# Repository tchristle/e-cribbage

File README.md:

# e-cribbage
SMT LED Cribbage Board

**To-Do List**
**-----------------------------------------------------------------**
* Schematic
	- [x] assign different symbols to P1 and P2 LEDs
	- [x] assign correct parts numbers to switch and CR2032 symbols
	- [ ] assign final values to LED current limiting resistor
* Layout
	- [x] modify CR2032 footprint to match selected clip
	- [x] modify B5 footprint to match selected slide switch
	- [x] assign common footprint to all capacitors
	- [x] update footprint for S1-S4 tactile push buttons
	- [x] generate gerbers and drill
	- [ ] fix up silk screen on foot prints
* Mechanical
	- [ ] design acrylic cover
	- [ ] update view showing current buttons
* BOM
	- [x] generate BOM from KiCAD schematic
	- [ ] attach Digikey PNs to BOM
	- [X] down select LEDs and colors
	- [x] down select slide switch
	- [x] down select tactile push button
	- [ ] generate Digikey cart from BOM
	- [x] get pricing on PCB
	- [x] get pricing on stencils
	- [ ] get pricing on pick and place assembly
* Software
	- [ ] debug flash store and recall functions
	- [ ] replace for loops and counters with timers in LPM0
	- [X] implement peg swap timer
	- [X] implement Elapsed Time Indicator
* Prototype
	- [x] drive sample LEDs with limit resistor to set brightness level
	- [X] analyze battery life with CR2032 cell
	- [x] interface ez430 with single shifter register

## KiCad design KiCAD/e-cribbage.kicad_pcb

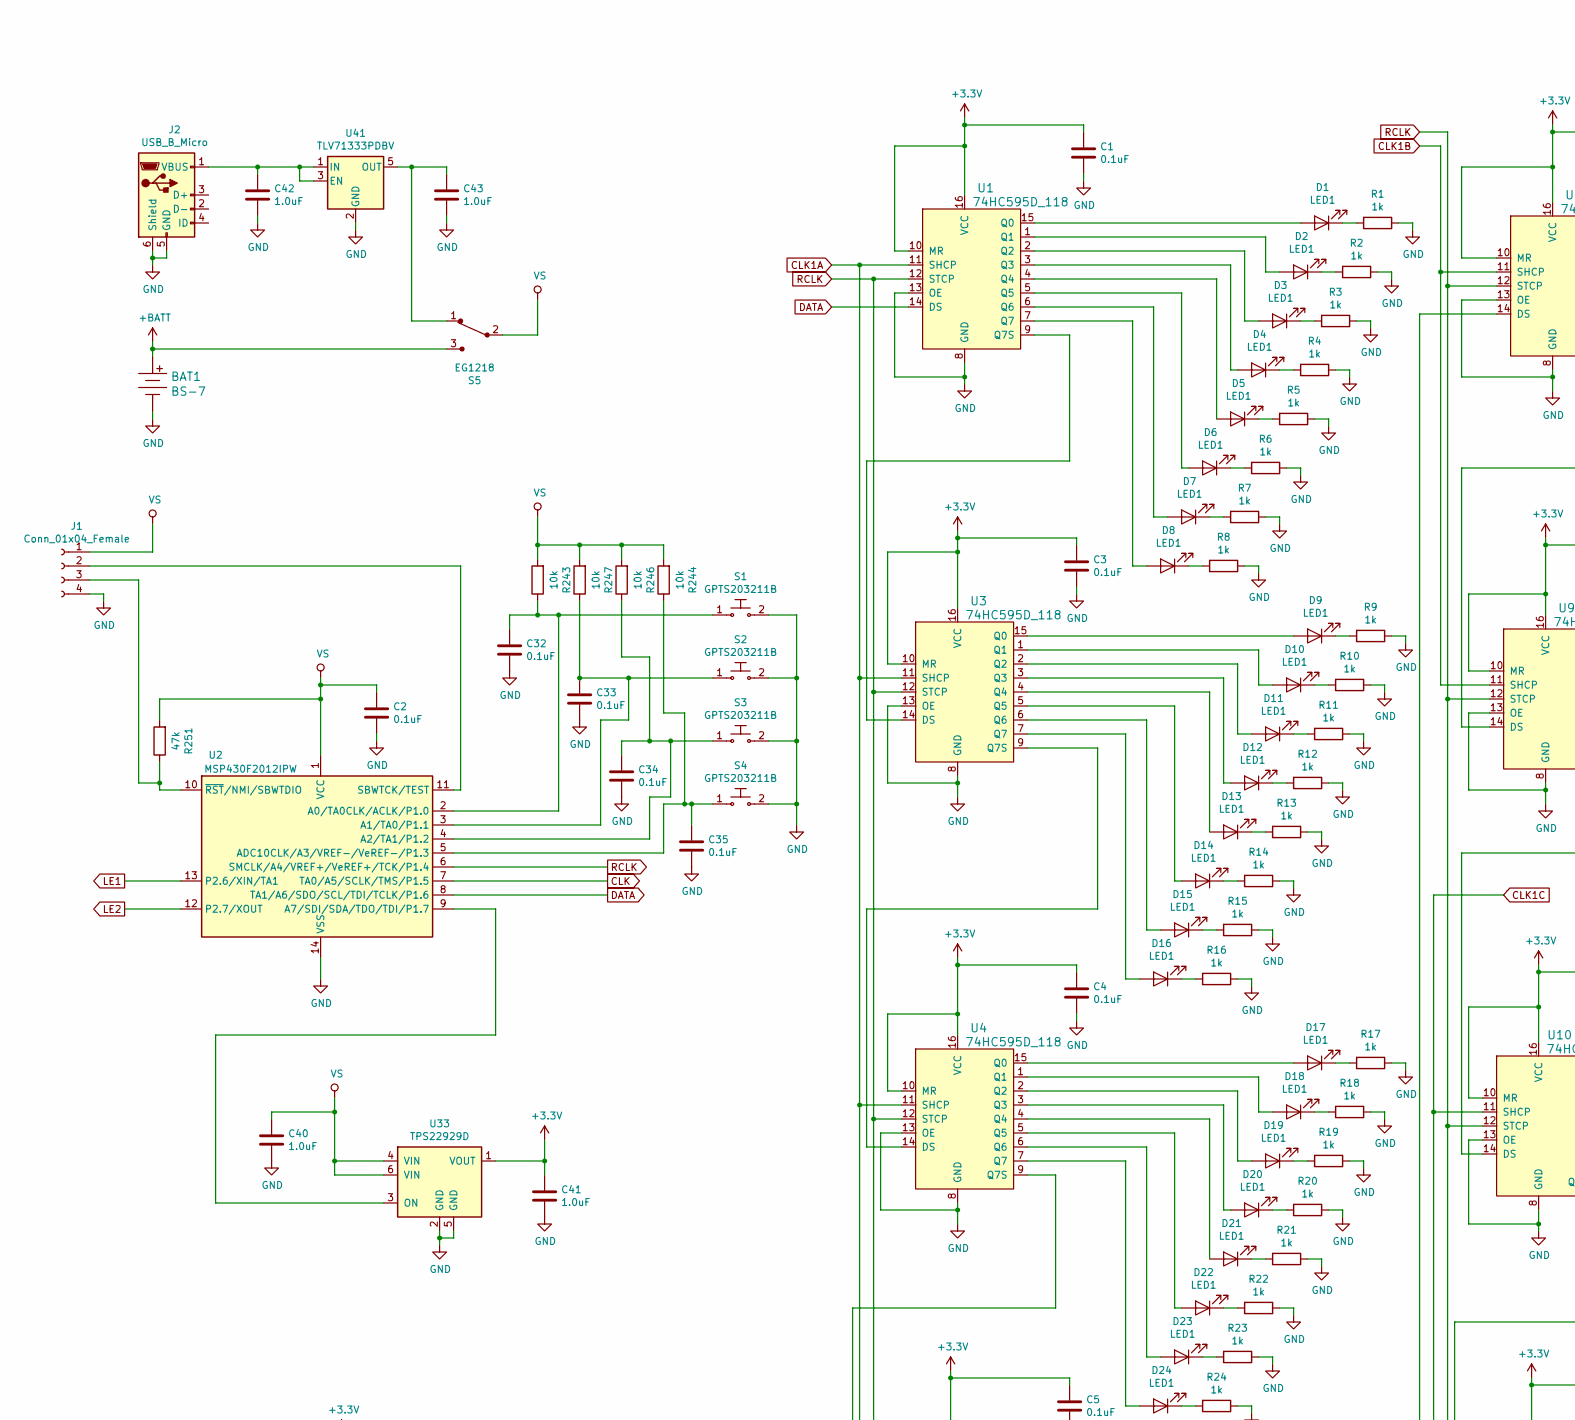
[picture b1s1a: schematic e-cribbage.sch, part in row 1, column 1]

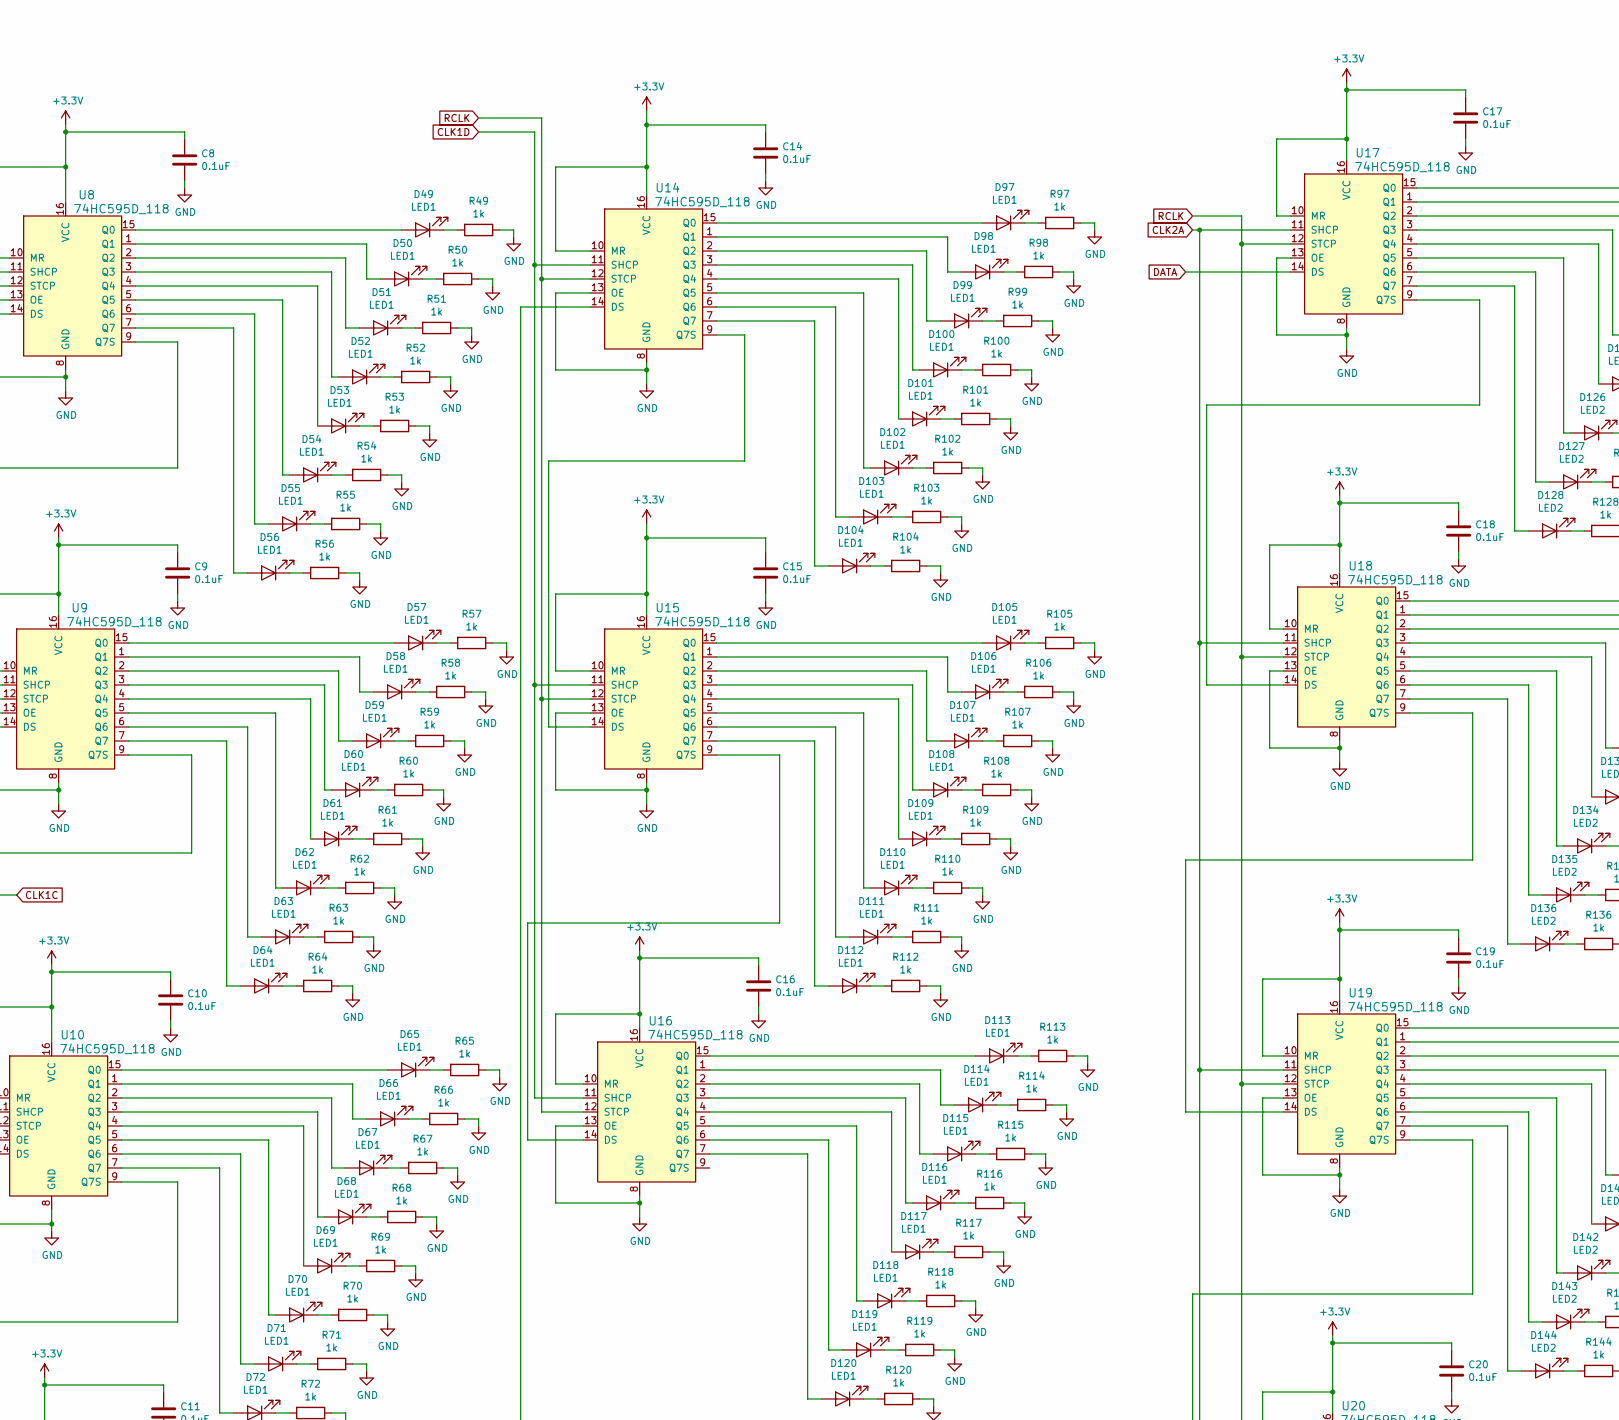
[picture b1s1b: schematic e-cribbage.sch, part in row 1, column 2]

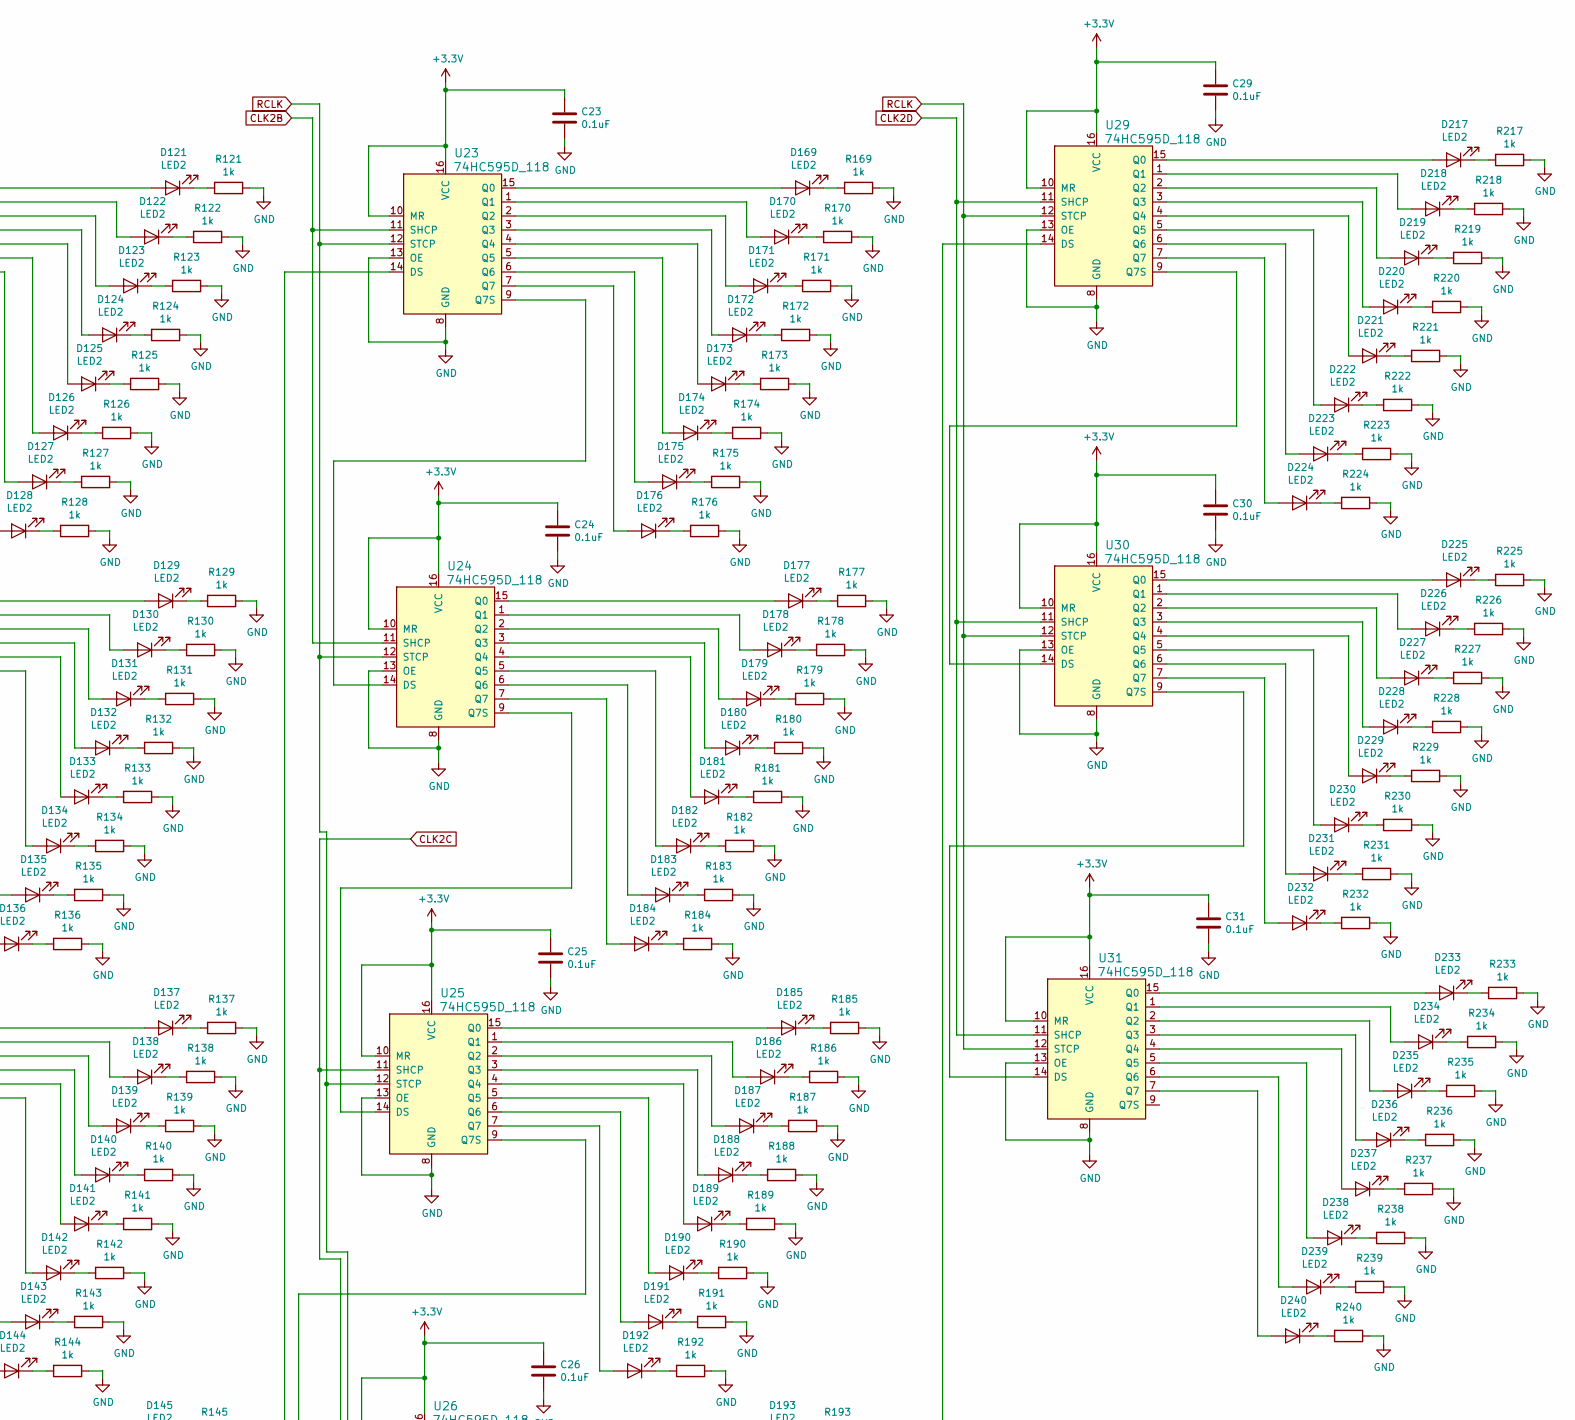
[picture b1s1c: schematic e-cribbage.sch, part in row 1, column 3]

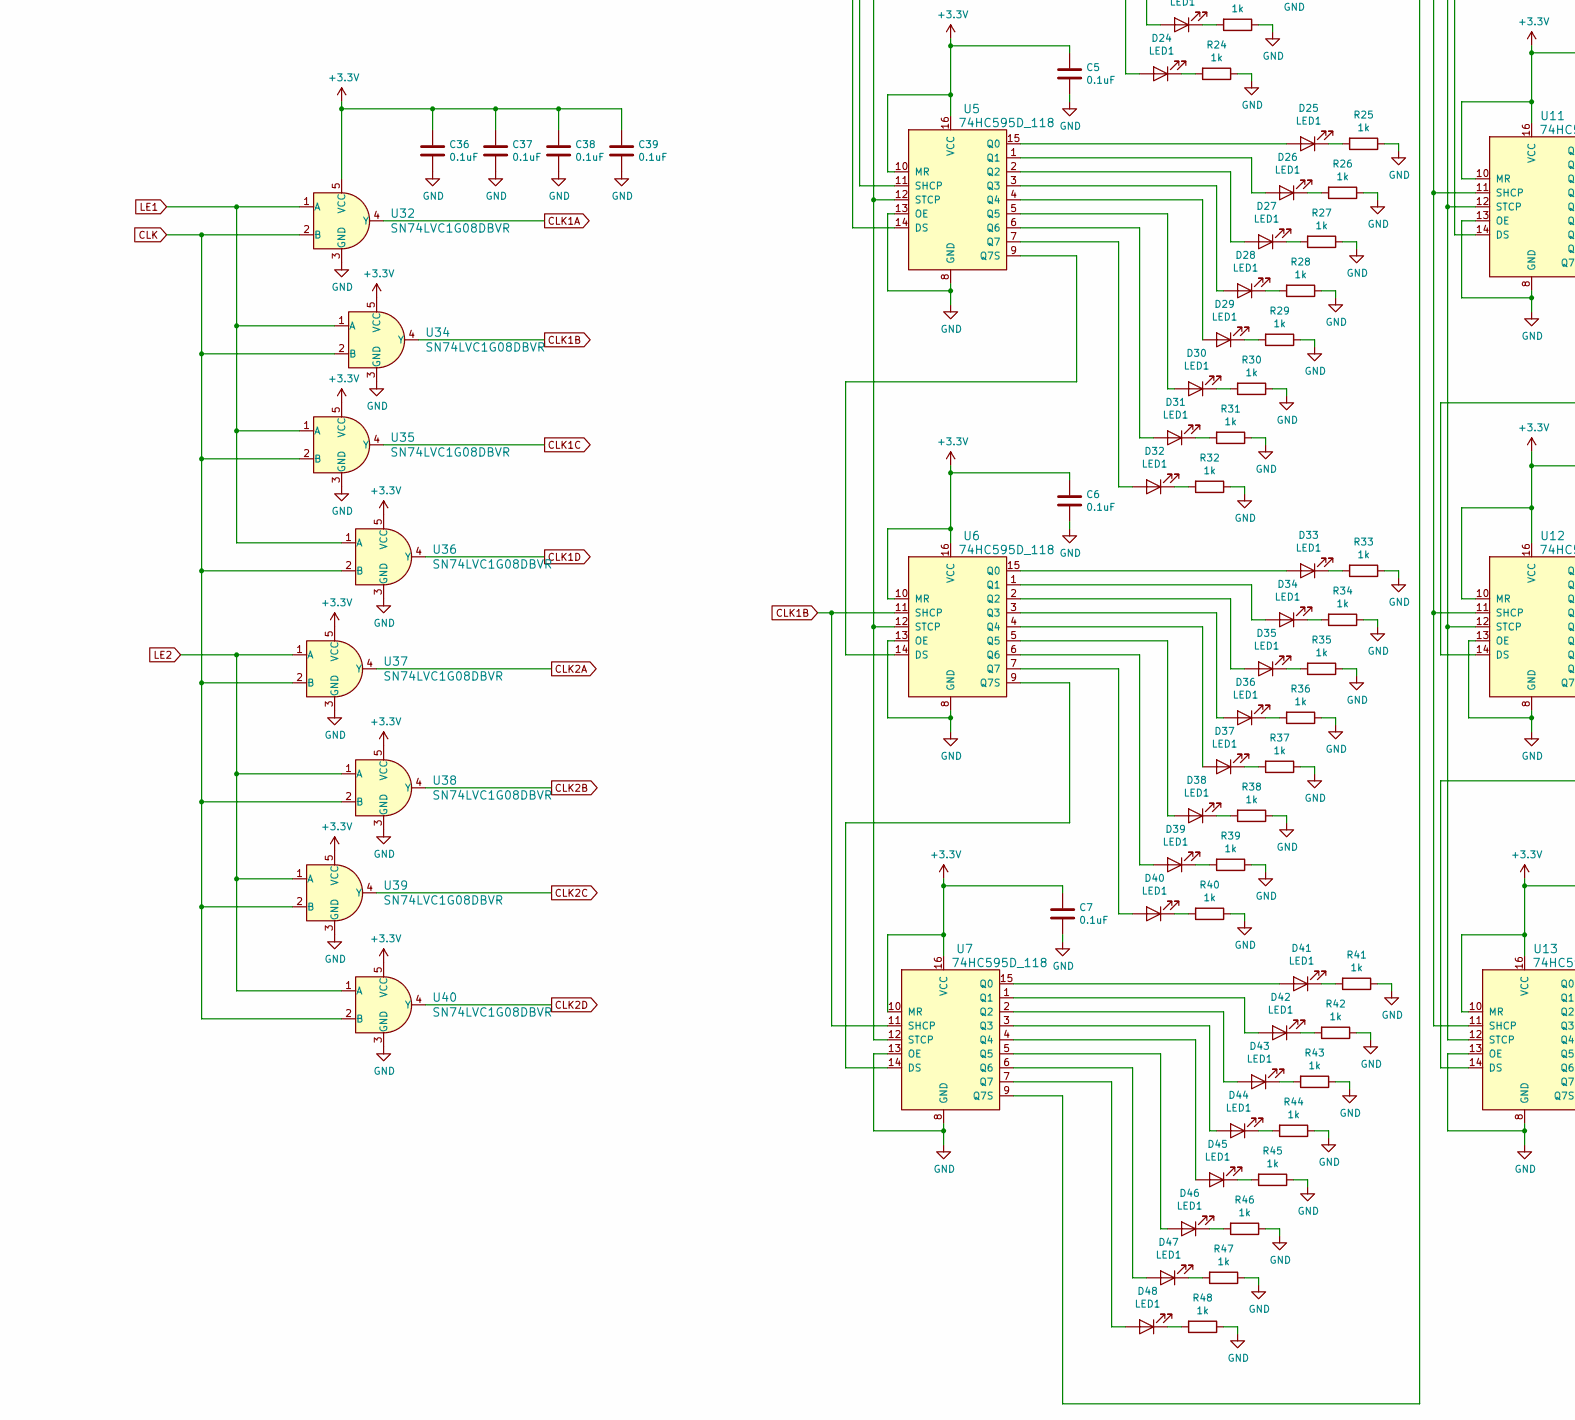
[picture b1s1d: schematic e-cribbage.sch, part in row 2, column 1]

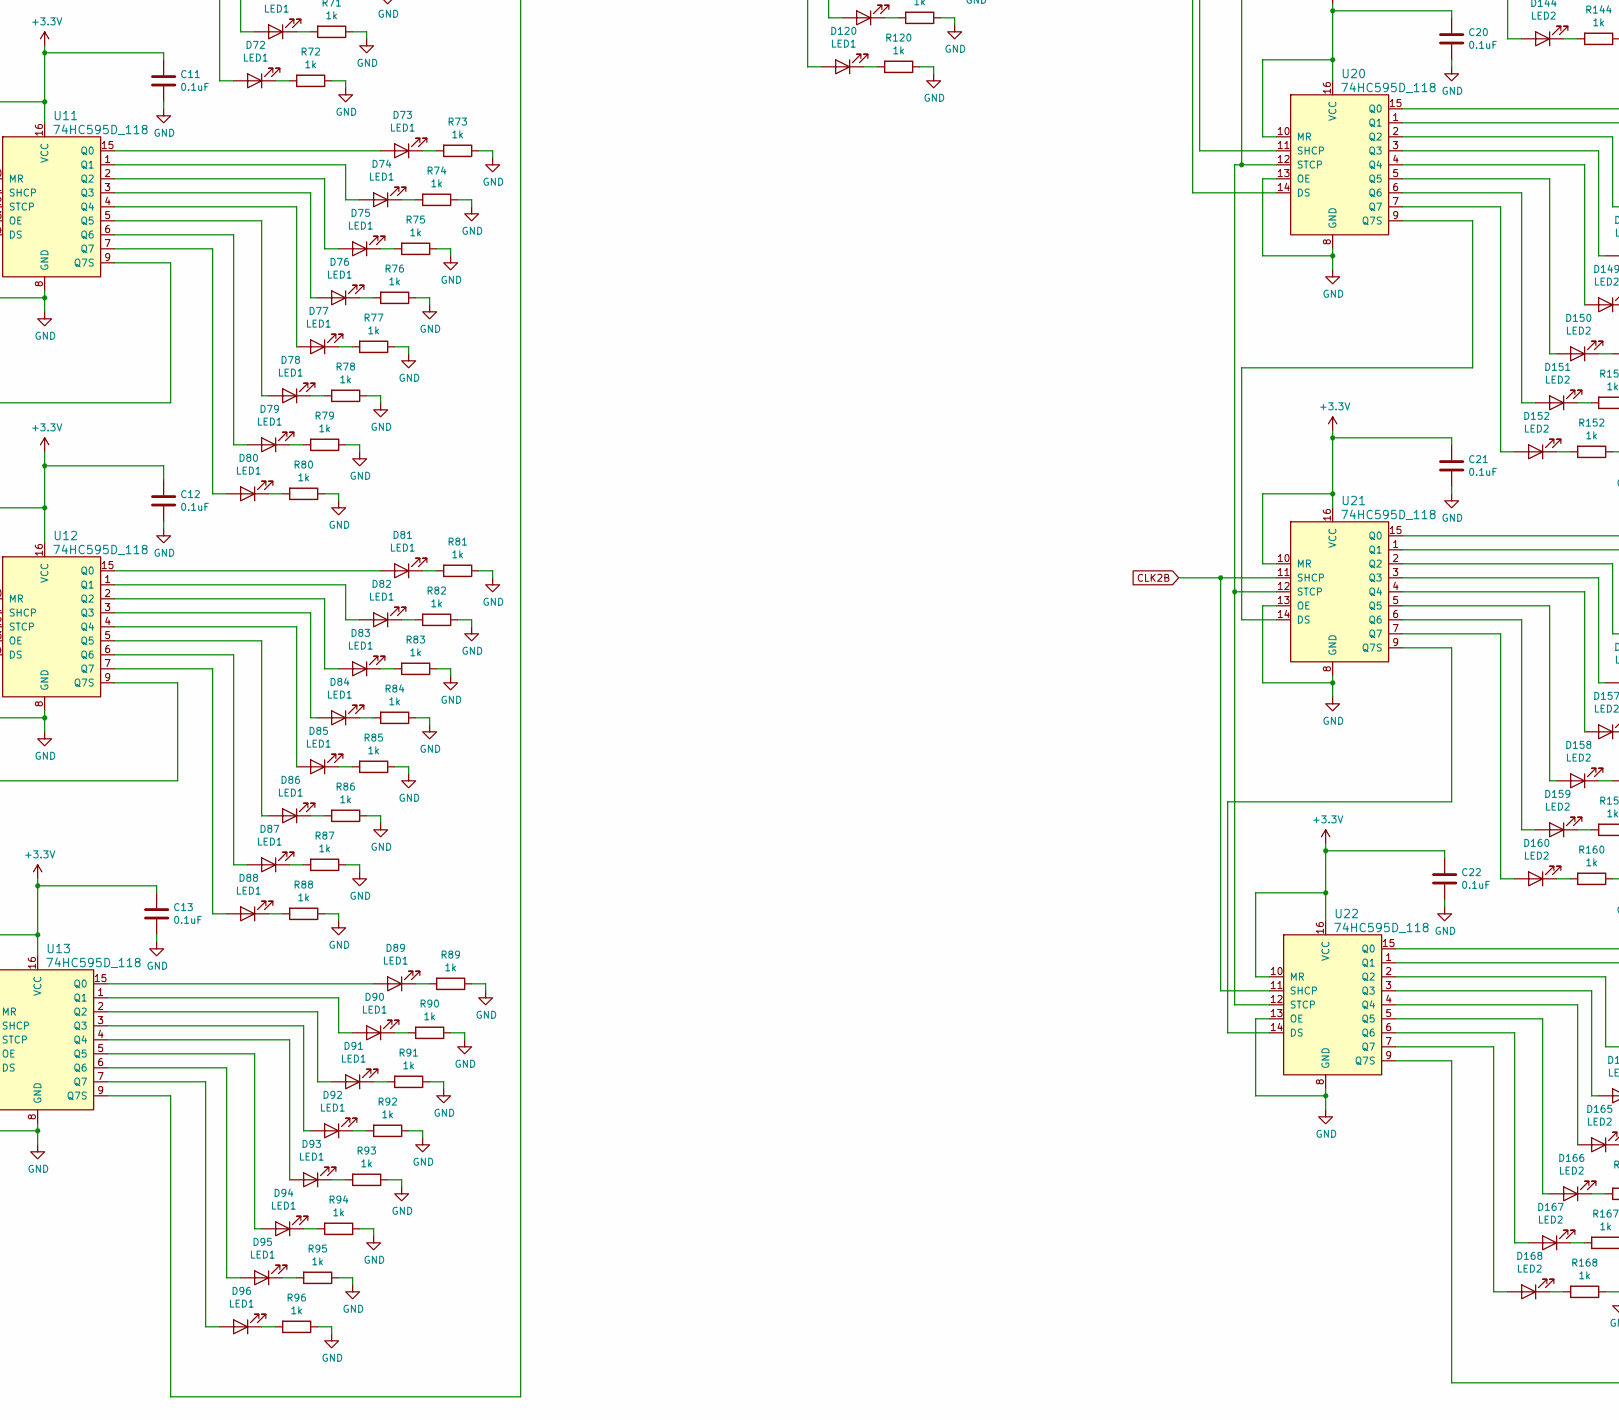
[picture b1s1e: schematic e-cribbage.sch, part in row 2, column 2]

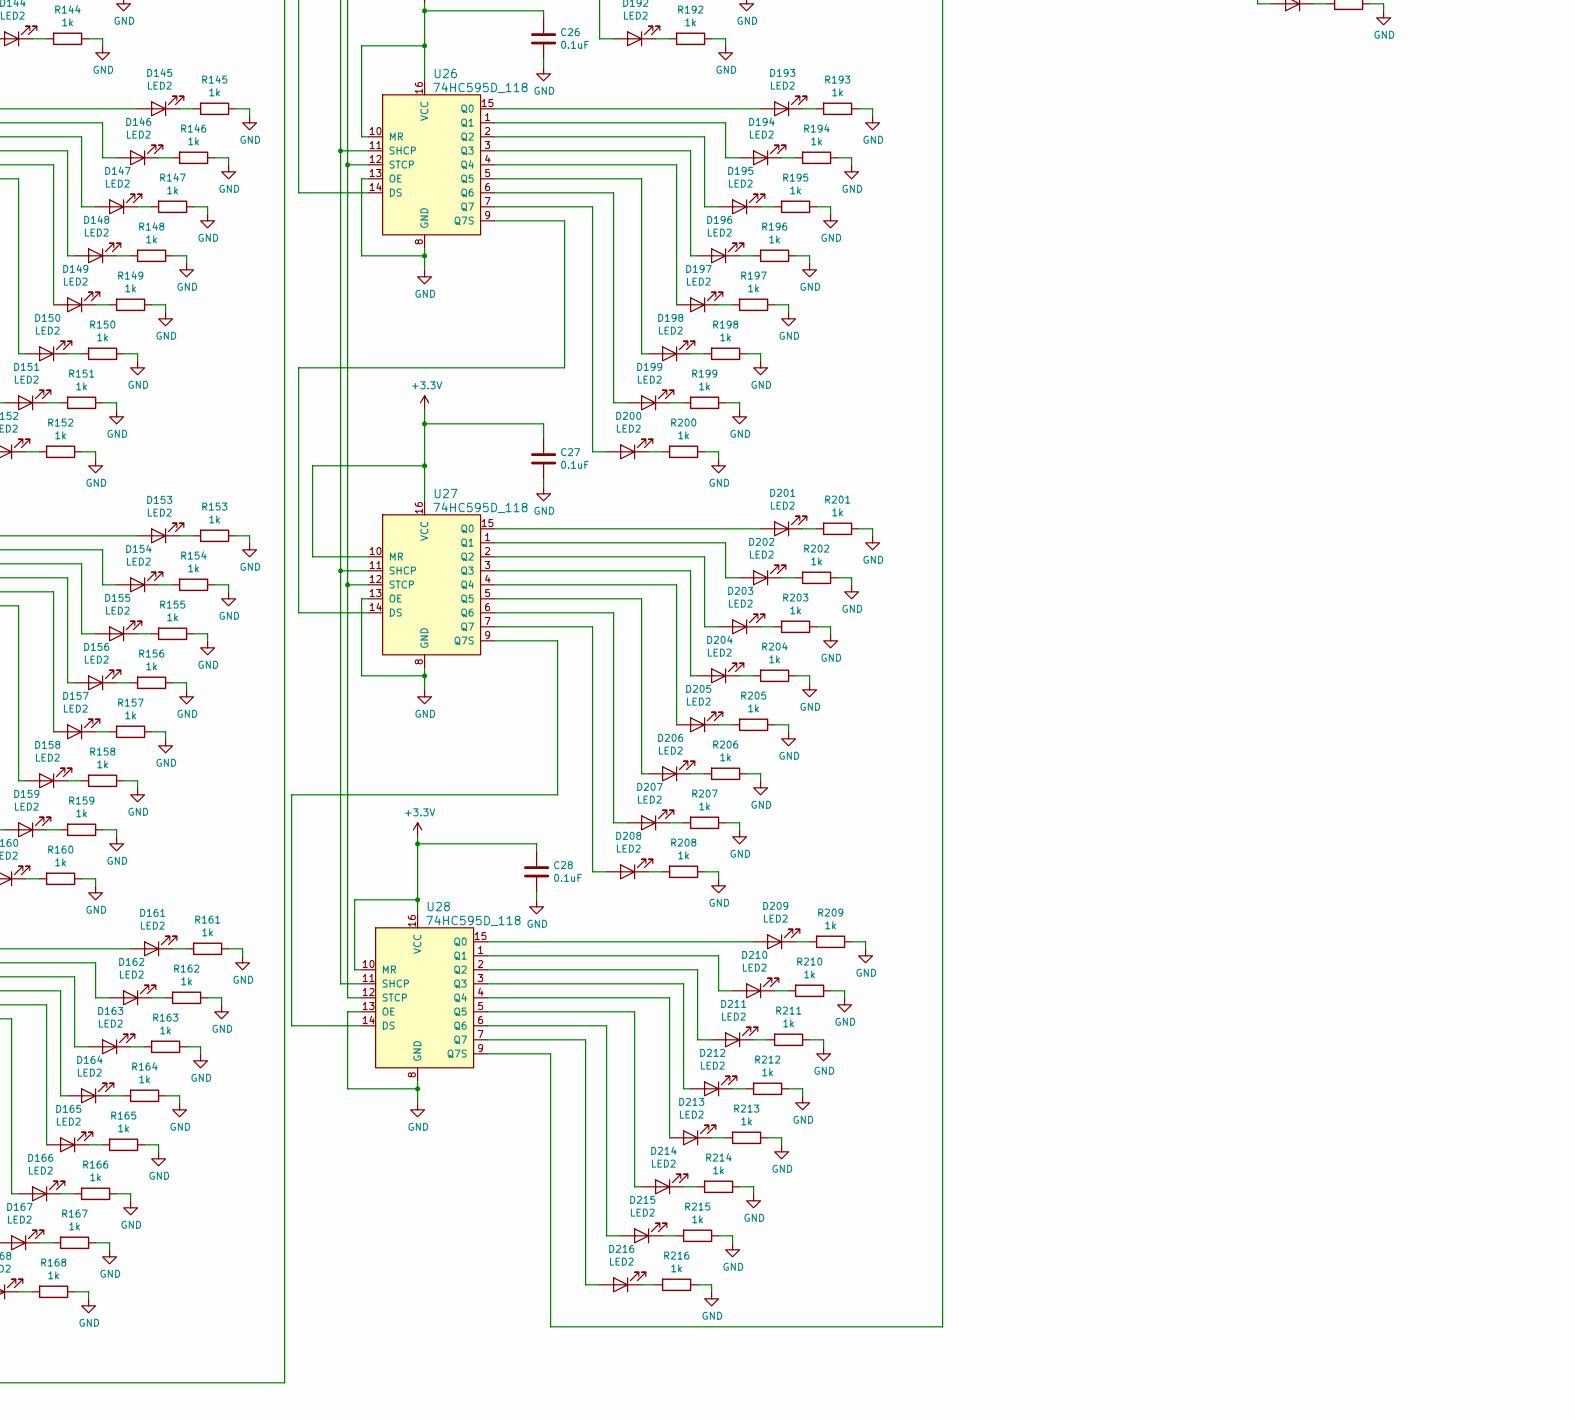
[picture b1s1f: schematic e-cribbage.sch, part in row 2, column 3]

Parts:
BAT1: BS-7; Keystone_1058_1x2032-CoinCell; MPN BS-7; Digi-Key_PN BS-7-ND
C1, C2, C3, C4, C5, C6, C7, C8, C9, C10, C11, C12, C13, C14, C15, C16, C17, C18, C19, C20, C21, C22, C23, C24, C25, C26, C27, C28, C29, C30, C31, C32, C33, C34, C35, C36, C37, C38, C39: 0.1uF; C_0603_1608Metric_Pad1.05x0.95mm_HandSolder
C40, C41, C42, C43: 1.0uF; C_0603_1608Metric_Pad1.05x0.95mm_HandSolder
D1, D2, D3, D4, D5, D6, D7, D8, D9, D10, D11, D12, D13, D14, D15, D16, D17, D18, D19, D20, D21, D22, D23, D24, D25, D26, D27, D28, D29, D30, D31, D32, D33, D34, D35, D36, D37, D38, D39, D40, D41, D42, D43, D44, D45, D46, D47, D48, D49, D50, D51, D52, D53, D54, D55, D56, D57, D58, D59, D60, D61, D62, D63, D64, D65, D66, D67, D68, D69, D70, D71, D72, D73, D74, D75, D76, D77, D78, D79, D80, D81, D82, D83, D84, D85, D86, D87, D88, D89, D90, D91, D92, D93, D94, D95, D96, D97, D98, D99, D100, D101, D102, D103, D104, D105, D106, D107, D108, D109, D110, D111, D112, D113, D114, D115, D116, D117, D118, D119, D120: LED1; LED_0603
D121, D122, D123, D124, D125, D126, D127, D128, D129, D130, D131, D132, D133, D134, D135, D136, D137, D138, D139, D140, D141, D142, D143, D144, D145, D146, D147, D148, D149, D150, D151, D152, D153, D154, D155, D156, D157, D158, D159, D160, D161, D162, D163, D164, D165, D166, D167, D168, D169, D170, D171, D172, D173, D174, D175, D176, D177, D178, D179, D180, D181, D182, D183, D184, D185, D186, D187, D188, D189, D190, D191, D192, D193, D194, D195, D196, D197, D198, D199, D200, D201, D202, D203, D204, D205, D206, D207, D208, D209, D210, D211, D212, D213, D214, D215, D216, D217, D218, D219, D220, D221, D222, D223, D224, D225, D226, D227, D228, D229, D230, D231, D232, D233, D234, D235, D236, D237, D238, D239, D240: LED2; LED_0603
J1: Conn_01x04_Female; PinHeader_1x04_P1.27mm_Vertical
J2: USB_B_Micro; USB_Micro-B_Molex_47346-0001
R1, R2, R3, R4, R5, R6, R7, R8, R9, R10, R11, R12, R13, R14, R15, R16, R17, R18, R19, R20, R21, R22, R23, R24, R25, R26, R27, R28, R29, R30, R31, R32, R33, R34, R35, R36, R37, R38, R39, R40, R41, R42, R43, R44, R45, R46, R47, R48, R49, R50, R51, R52, R53, R54, R55, R56, R57, R58, R59, R60, R61, R62, R63, R64, R65, R66, R67, R68, R69, R70, R71, R72, R73, R74, R75, R76, R77, R78, R79, R80, R81, R82, R83, R84, R85, R86, R87, R88, R89, R90, R91, R92, R93, R94, R95, R96, R97, R98, R99, R100, R101, R102, R103, R104, R105, R106, R107, R108, R109, R110, R111, R112, R113, R114, R115, R116, R117, R118, R119, R120, R121, R122, R123, R124, R125, R126, R127, R128, R129, R130, R131, R132, R133, R134, R135, R136, R137, R138, R139, R140, R141, R142, R143, R144, R145, R146, R147, R148, R149, R150, R151, R152, R153, R154, R155, R156, R157, R158, R159, R160, R161, R162, R163, R164, R165, R166, R167, R168, R169, R170, R171, R172, R173, R174, R175, R176, R177, R178, R179, R180, R181, R182, R183, R184, R185, R186, R187, R188, R189, R190, R191, R192, R193, R194, R195, R196, R197, R198, R199, R200, R201, R202, R203, R204, R205, R206, R207, R208, R209, R210, R211, R212, R213, R214, R215, R216, R217, R218, R219, R220, R221, R222, R223, R224, R225, R226, R227, R228, R229, R230, R231, R232, R233, R234, R235, R236, R237, R238, R239, R240: 1k; R_0603
R243, R244, R246, R247: 10k; R_0603
R251: 47k; R_0603
S1, S2, S3, S4: GPTS203211B; KS12R22; MPN GPTS203211B; Digi-Key_PN CW181-ND
S5: EG1218; SW_SPDT_CK-JS102011SAQN; MPN EG1218; Digi-Key_PN EG1903-ND
U1, U3, U4, U5, U6, U7, U8, U9, U10, U11, U12, U13, U14, U15, U16, U17, U18, U19, U20, U21, U22, U23, U24, U25, U26, U27, U28, U29, U30, U31: 74HC595D_118; TSSOP-16_W4.40mm; MPN 74HC595D,118; Digi-Key_PN 1727-2821-1-ND
U2: MSP430F2012IPW; TSSOP-14_W4.4mm
U32, U34, U35, U36, U37, U38, U39, U40: SN74LVC1G08DBVR; SOT-753; MPN SN74LVC1G08DBVR; Digi-Key_PN 296-11601-1-ND
U33: TPS22929D; SOT-23-6
U41: TLV71333PDBV; SOT-23-5

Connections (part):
+3V3: C1.1, C3.1, C4.1, C5.1, C6.1, C7.1, C8.1, C9.1, C10.1, C11.1, C12.1, C13.1, C14.1, C15.1, C16.1, C17.1, C18.1, C19.1, C20.1, C21.1, C22.1, C23.1, C24.1, C25.1, C26.1, C27.1, C28.1, C29.1, C30.1, C31.1, C36.1, C37.1, C38.1, C39.1, C41.1, U1.10 (MR), U1.16 (VCC), U3.10 (MR), U3.16 (VCC), U4.10 (MR), U4.16 (VCC), U5.10 (MR), U5.16 (VCC), U6.10 (MR), U6.16 (VCC), U7.10 (MR), U7.16 (VCC), U8.10 (MR), U8.16 (VCC), U9.10 (MR), U9.16 (VCC), U10.10 (MR), U10.16 (VCC), U11.10 (MR), U11.16 (VCC), U12.10 (MR), U12.16 (VCC), U13.10 (MR), U13.16 (VCC), U14.10 (MR), U14.16 (VCC), U15.10 (MR), U15.16 (VCC), U16.10 (MR), U16.16 (VCC), U17.10 (MR), U17.16 (VCC), U18.10 (MR), U18.16 (VCC), U19.10 (MR), U19.16 (VCC), U20.10 (MR), U20.16 (VCC), U21.10 (MR), U21.16 (VCC), U22.10 (MR), U22.16 (VCC), U23.10 (MR), U23.16 (VCC), U24.10 (MR)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
+BATT: BAT1.1, S5.3
CLK: U2.7 (TA0/A5/SCLK/TMS/P1.5), U32.2 (B), U34.2 (B), U35.2 (B), U36.2 (B), U37.2 (B), U38.2 (B), U39.2 (B), U40.2 (B)
CLK1A: U1.11 (SHCP), U3.11 (SHCP), U4.11 (SHCP), U5.11 (SHCP), U32.4 (Y)
CLK1B: U6.11 (SHCP), U7.11 (SHCP), U8.11 (SHCP), U9.11 (SHCP), U34.4 (Y)
CLK1C: U10.11 (SHCP), U11.11 (SHCP), U12.11 (SHCP), U13.11 (SHCP), U35.4 (Y)
CLK1D: U14.11 (SHCP), U15.11 (SHCP), U16.11 (SHCP), U36.4 (Y)
CLK2A: U17.11 (SHCP), U18.11 (SHCP), U19.11 (SHCP), U20.11 (SHCP), U37.4 (Y)
CLK2B: U21.11 (SHCP), U22.11 (SHCP), U23.11 (SHCP), U24.11 (SHCP), U38.4 (Y)
CLK2C: U25.11 (SHCP), U26.11 (SHCP), U27.11 (SHCP), U28.11 (SHCP), U39.4 (Y)
CLK2D: U29.11 (SHCP), U30.11 (SHCP), U31.11 (SHCP), U40.4 (Y)
DATA: U1.14 (DS), U2.8 (TA1/A6/SDO/SCL/TDI/TCLK/P1.6), U17.14 (DS)
GND: BAT1.2, C1.2, C2.2, C3.2, C4.2, C5.2, C6.2, C7.2, C8.2, C9.2, C10.2, C11.2, C12.2, C13.2, C14.2, C15.2, C16.2, C17.2, C18.2, C19.2, C20.2, C21.2, C22.2, C23.2, C24.2, C25.2, C26.2, C27.2, C28.2, C29.2, C30.2, C31.2, C32.2, C33.2, C34.2, C35.2, C36.2, C37.2, C38.2, C39.2, C40.2, C41.2, C42.2, C43.2, J1.4, J2.5 (GND), J2.6 (Shield), R1.1, R2.1, R3.1, R4.1, R5.1, R6.1, R7.1, R8.1, R9.1, R10.1, R11.1, R12.1, R13.1, R14.1, R15.1, R16.1, R17.1, R18.1, R19.1, R20.1, R21.1, R22.1, R23.1, R24.1, R25.1, R26.1, R27.1, R28.1, R29.1, R30.1, R31.1, R32.1, R33.1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
LE1: U2.13 (P2.6/XIN/TA1), U32.1 (A), U34.1 (A), U35.1 (A), U36.1 (A)
LE2: U2.12 (P2.7/XOUT), U37.1 (A), U38.1 (A), U39.1 (A), U40.1 (A)
unnamed: C32.1, R243.1, S1.1, U2.2 (A0/TA0CLK/ACLK/P1.0)
unnamed: C33.1, R247.1, S2.1, U2.3 (A1/TA0/P1.1)
unnamed: C34.1, R246.1, S3.1, U2.4 (A2/TA1/P1.2)
unnamed: C35.1, R244.1, S4.1, U2.5 (ADC10CLK/A3/VREF-/VeREF-/P1.3)
unnamed: C42.1, J2.1 (VBUS), U41.1 (IN), U41.3 (EN)
unnamed: C43.1, S5.1, U41.5 (OUT)
unnamed: D1.1 (K), R1.2
unnamed: D1.2 (A), U1.15 (Q0)
unnamed: D2.1 (K), R2.2
unnamed: D2.2 (A), U1.1 (Q1)
unnamed: D3.1 (K), R3.2
unnamed: D3.2 (A), U1.2 (Q2)
unnamed: D4.1 (K), R4.2
unnamed: D4.2 (A), U1.3 (Q3)
unnamed: D5.1 (K), R5.2
unnamed: D5.2 (A), U1.4 (Q4)
unnamed: D6.1 (K), R6.2
unnamed: D6.2 (A), U1.5 (Q5)
unnamed: D7.1 (K), R7.2
unnamed: D7.2 (A), U1.6 (Q6)
unnamed: D8.1 (K), R8.2
unnamed: D8.2 (A), U1.7 (Q7)
unnamed: D9.1 (K), R9.2
unnamed: D9.2 (A), U3.15 (Q0)
unnamed: D10.1 (K), R10.2
unnamed: D10.2 (A), U3.1 (Q1)
unnamed: D11.1 (K), R11.2
unnamed: D11.2 (A), U3.2 (Q2)
unnamed: D12.1 (K), R12.2
unnamed: D12.2 (A), U3.3 (Q3)
unnamed: D13.1 (K), R13.2
unnamed: D13.2 (A), U3.4 (Q4)
unnamed: D14.1 (K), R14.2
unnamed: D14.2 (A), U3.5 (Q5)
unnamed: D15.1 (K), R15.2
unnamed: D15.2 (A), U3.6 (Q6)
unnamed: D16.1 (K), R16.2
unnamed: D16.2 (A), U3.7 (Q7)
unnamed: D17.1 (K), R17.2
unnamed: D17.2 (A), U4.15 (Q0)
unnamed: D18.1 (K), R18.2
unnamed: D18.2 (A), U4.1 (Q1)
unnamed: D19.1 (K), R19.2
unnamed: D19.2 (A), U4.2 (Q2)
unnamed: D20.1 (K), R20.2
unnamed: D20.2 (A), U4.3 (Q3)
unnamed: D21.1 (K), R21.2
unnamed: D21.2 (A), U4.4 (Q4)
unnamed: D22.1 (K), R22.2
unnamed: D22.2 (A), U4.5 (Q5)
unnamed: D23.1 (K), R23.2
unnamed: D23.2 (A), U4.6 (Q6)
unnamed: D24.1 (K), R24.2
unnamed: D24.2 (A), U4.7 (Q7)
unnamed: D25.1 (K), R25.2
unnamed: D25.2 (A), U5.15 (Q0)
unnamed: D26.1 (K), R26.2
unnamed: D26.2 (A), U5.1 (Q1)
unnamed: D27.1 (K), R27.2
unnamed: D27.2 (A), U5.2 (Q2)
unnamed: D28.1 (K), R28.2
unnamed: D28.2 (A), U5.3 (Q3)
unnamed: D29.1 (K), R29.2
unnamed: D29.2 (A), U5.4 (Q4)
unnamed: D30.1 (K), R30.2
unnamed: D30.2 (A), U5.5 (Q5)
unnamed: D31.1 (K), R31.2
unnamed: D31.2 (A), U5.6 (Q6)
unnamed: D32.1 (K), R32.2
unnamed: D32.2 (A), U5.7 (Q7)
unnamed: D33.1 (K), R33.2
unnamed: D33.2 (A), U6.15 (Q0)
unnamed: D34.1 (K), R34.2
unnamed: D34.2 (A), U6.1 (Q1)
unnamed: D35.1 (K), R35.2
unnamed: D35.2 (A), U6.2 (Q2)
unnamed: D36.1 (K), R36.2
unnamed: D36.2 (A), U6.3 (Q3)
unnamed: D37.1 (K), R37.2
unnamed: D37.2 (A), U6.4 (Q4)
unnamed: D38.1 (K), R38.2
unnamed: D38.2 (A), U6.5 (Q5)
unnamed: D39.1 (K), R39.2
unnamed: D39.2 (A), U6.6 (Q6)
unnamed: D40.1 (K), R40.2
unnamed: D40.2 (A), U6.7 (Q7)
unnamed: D41.1 (K), R41.2
unnamed: D41.2 (A), U7.15 (Q0)
unnamed: D42.1 (K), R42.2
unnamed: D42.2 (A), U7.1 (Q1)
unnamed: D43.1 (K), R43.2
unnamed: D43.2 (A), U7.2 (Q2)
unnamed: D44.1 (K), R44.2
unnamed: D44.2 (A), U7.3 (Q3)
unnamed: D45.1 (K), R45.2
unnamed: D45.2 (A), U7.4 (Q4)
unnamed: D46.1 (K), R46.2
unnamed: D46.2 (A), U7.5 (Q5)
unnamed: D47.1 (K), R47.2
unnamed: D47.2 (A), U7.6 (Q6)
unnamed: D48.1 (K), R48.2
unnamed: D48.2 (A), U7.7 (Q7)
unnamed: D49.1 (K), R49.2
unnamed: D49.2 (A), U8.15 (Q0)
unnamed: D50.1 (K), R50.2
unnamed: D50.2 (A), U8.1 (Q1)
unnamed: D51.1 (K), R51.2
unnamed: D51.2 (A), U8.2 (Q2)
unnamed: D52.1 (K), R52.2
unnamed: D52.2 (A), U8.3 (Q3)
unnamed: D53.1 (K), R53.2
unnamed: D53.2 (A), U8.4 (Q4)
unnamed: D54.1 (K), R54.2
unnamed: D54.2 (A), U8.5 (Q5)
unnamed: D55.1 (K), R55.2
unnamed: D55.2 (A), U8.6 (Q6)
unnamed: D56.1 (K), R56.2
unnamed: D56.2 (A), U8.7 (Q7)
unnamed: D57.1 (K), R57.2
unnamed: D57.2 (A), U9.15 (Q0)
unnamed: D58.1 (K), R58.2
unnamed: D58.2 (A), U9.1 (Q1)
unnamed: D59.1 (K), R59.2
unnamed: D59.2 (A), U9.2 (Q2)
unnamed: D60.1 (K), R60.2
unnamed: D60.2 (A), U9.3 (Q3)
unnamed: D61.1 (K), R61.2
unnamed: D61.2 (A), U9.4 (Q4)
unnamed: D62.1 (K), R62.2
unnamed: D62.2 (A), U9.5 (Q5)
unnamed: D63.1 (K), R63.2
unnamed: D63.2 (A), U9.6 (Q6)
unnamed: D64.1 (K), R64.2
unnamed: D64.2 (A), U9.7 (Q7)
unnamed: D65.1 (K), R65.2
unnamed: D65.2 (A), U10.15 (Q0)
unnamed: D66.1 (K), R66.2
unnamed: D66.2 (A), U10.1 (Q1)
unnamed: D67.1 (K), R67.2
unnamed: D67.2 (A), U10.2 (Q2)
unnamed: D68.1 (K), R68.2
unnamed: D68.2 (A), U10.3 (Q3)
unnamed: D69.1 (K), R69.2
unnamed: D69.2 (A), U10.4 (Q4)
unnamed: D70.1 (K), R70.2
unnamed: D70.2 (A), U10.5 (Q5)
unnamed: D71.1 (K), R71.2
unnamed: D71.2 (A), U10.6 (Q6)
unnamed: D72.1 (K), R72.2
unnamed: D72.2 (A), U10.7 (Q7)
unnamed: D73.1 (K), R73.2
unnamed: D73.2 (A), U11.15 (Q0)
unnamed: D74.1 (K), R74.2
unnamed: D74.2 (A), U11.1 (Q1)
unnamed: D75.1 (K), R75.2
unnamed: D75.2 (A), U11.2 (Q2)
unnamed: D76.1 (K), R76.2
unnamed: D76.2 (A), U11.3 (Q3)
unnamed: D77.1 (K), R77.2
unnamed: D77.2 (A), U11.4 (Q4)
unnamed: D78.1 (K), R78.2
unnamed: D78.2 (A), U11.5 (Q5)
unnamed: D79.1 (K), R79.2
unnamed: D79.2 (A), U11.6 (Q6)
unnamed: D80.1 (K), R80.2
unnamed: D80.2 (A), U11.7 (Q7)
unnamed: D81.1 (K), R81.2
unnamed: D81.2 (A), U12.15 (Q0)
unnamed: D82.1 (K), R82.2
unnamed: D82.2 (A), U12.1 (Q1)
unnamed: D83.1 (K), R83.2
unnamed: D83.2 (A), U12.2 (Q2)
unnamed: D84.1 (K), R84.2
unnamed: D84.2 (A), U12.3 (Q3)
unnamed: D85.1 (K), R85.2
unnamed: D85.2 (A), U12.4 (Q4)
unnamed: D86.1 (K), R86.2
unnamed: D86.2 (A), U12.5 (Q5)
unnamed: D87.1 (K), R87.2
unnamed: D87.2 (A), U12.6 (Q6)
unnamed: D88.1 (K), R88.2
unnamed: D88.2 (A), U12.7 (Q7)
unnamed: D89.1 (K), R89.2
unnamed: D89.2 (A), U13.15 (Q0)
unnamed: D90.1 (K), R90.2
unnamed: D90.2 (A), U13.1 (Q1)
unnamed: D91.1 (K), R91.2
unnamed: D91.2 (A), U13.2 (Q2)
unnamed: D92.1 (K), R92.2
unnamed: D92.2 (A), U13.3 (Q3)
unnamed: D93.1 (K), R93.2
unnamed: D93.2 (A), U13.4 (Q4)
unnamed: D94.1 (K), R94.2
unnamed: D94.2 (A), U13.5 (Q5)
unnamed: D95.1 (K), R95.2
unnamed: D95.2 (A), U13.6 (Q6)
unnamed: D96.1 (K), R96.2
unnamed: D96.2 (A), U13.7 (Q7)
unnamed: D97.1 (K), R97.2
unnamed: D97.2 (A), U14.15 (Q0)
unnamed: D98.1 (K), R98.2
unnamed: D98.2 (A), U14.1 (Q1)
unnamed: D99.1 (K), R99.2
unnamed: D99.2 (A), U14.2 (Q2)
unnamed: D100.1 (K), R100.2
unnamed: D100.2 (A), U14.3 (Q3)
unnamed: D101.1 (K), R101.2
unnamed: D101.2 (A), U14.4 (Q4)
unnamed: D102.1 (K), R102.2
unnamed: D102.2 (A), U14.5 (Q5)
unnamed: D103.1 (K), R103.2
unnamed: D103.2 (A), U14.6 (Q6)
unnamed: D104.1 (K), R104.2
unnamed: D104.2 (A), U14.7 (Q7)
unnamed: D105.1 (K), R105.2
unnamed: D105.2 (A), U15.15 (Q0)
unnamed: D106.1 (K), R106.2
unnamed: D106.2 (A), U15.1 (Q1)
unnamed: D107.1 (K), R107.2
unnamed: D107.2 (A), U15.2 (Q2)
unnamed: D108.1 (K), R108.2
unnamed: D108.2 (A), U15.3 (Q3)
unnamed: D109.1 (K), R109.2
unnamed: D109.2 (A), U15.4 (Q4)
unnamed: D110.1 (K), R110.2
unnamed: D110.2 (A), U15.5 (Q5)
unnamed: D111.1 (K), R111.2
unnamed: D111.2 (A), U15.6 (Q6)
unnamed: D112.1 (K), R112.2
unnamed: D112.2 (A), U15.7 (Q7)
unnamed: D113.1 (K), R113.2
unnamed: D113.2 (A), U16.15 (Q0)
unnamed: D114.1 (K), R114.2
unnamed: D114.2 (A), U16.1 (Q1)
unnamed: D115.1 (K), R115.2
unnamed: D115.2 (A), U16.2 (Q2)
unnamed: D116.1 (K), R116.2
unnamed: D116.2 (A), U16.3 (Q3)
unnamed: D117.1 (K), R117.2
unnamed: D117.2 (A), U16.4 (Q4)
unnamed: D118.1 (K), R118.2
unnamed: D118.2 (A), U16.5 (Q5)
unnamed: D119.1 (K), R119.2
unnamed: D119.2 (A), U16.6 (Q6)
unnamed: D120.1 (K), R120.2
unnamed: D120.2 (A), U16.7 (Q7)
unnamed: D121.1 (K), R121.2
unnamed: D121.2 (A), U17.15 (Q0)
unnamed: D122.1 (K), R122.2
unnamed: D122.2 (A), U17.1 (Q1)
unnamed: D123.1 (K), R123.2
unnamed: D123.2 (A), U17.2 (Q2)
unnamed: D124.1 (K), R124.2
unnamed: D124.2 (A), U17.3 (Q3)
unnamed: D125.1 (K), R125.2
unnamed: D125.2 (A), U17.4 (Q4)
unnamed: D126.1 (K), R126.2
unnamed: D126.2 (A), U17.5 (Q5)
unnamed: D127.1 (K), R127.2
unnamed: D127.2 (A), U17.6 (Q6)
unnamed: D128.1 (K), R128.2
unnamed: D128.2 (A), U17.7 (Q7)
unnamed: D129.1 (K), R129.2
unnamed: D129.2 (A), U18.15 (Q0)
unnamed: D130.1 (K), R130.2
unnamed: D130.2 (A), U18.1 (Q1)
unnamed: D131.1 (K), R131.2
unnamed: D131.2 (A), U18.2 (Q2)
unnamed: D132.1 (K), R132.2
unnamed: D132.2 (A), U18.3 (Q3)
unnamed: D133.1 (K), R133.2
unnamed: D133.2 (A), U18.4 (Q4)
unnamed: D134.1 (K), R134.2
unnamed: D134.2 (A), U18.5 (Q5)
unnamed: D135.1 (K), R135.2
unnamed: D135.2 (A), U18.6 (Q6)
unnamed: D136.1 (K), R136.2
unnamed: D136.2 (A), U18.7 (Q7)
unnamed: D137.1 (K), R137.2
unnamed: D137.2 (A), U19.15 (Q0)
unnamed: D138.1 (K), R138.2
unnamed: D138.2 (A), U19.1 (Q1)
unnamed: D139.1 (K), R139.2
unnamed: D139.2 (A), U19.2 (Q2)
unnamed: D140.1 (K), R140.2
unnamed: D140.2 (A), U19.3 (Q3)
unnamed: D141.1 (K), R141.2
unnamed: D141.2 (A), U19.4 (Q4)
unnamed: D142.1 (K), R142.2
unnamed: D142.2 (A), U19.5 (Q5)
unnamed: D143.1 (K), R143.2
unnamed: D143.2 (A), U19.6 (Q6)
unnamed: D144.1 (K), R144.2
unnamed: D144.2 (A), U19.7 (Q7)
unnamed: D145.1 (K), R145.2
unnamed: D145.2 (A), U20.15 (Q0)
unnamed: D146.1 (K), R146.2
unnamed: D146.2 (A), U20.1 (Q1)
unnamed: D147.1 (K), R147.2
unnamed: D147.2 (A), U20.2 (Q2)
unnamed: D148.1 (K), R148.2
unnamed: D148.2 (A), U20.3 (Q3)
unnamed: D149.1 (K), R149.2
unnamed: D149.2 (A), U20.4 (Q4)
unnamed: D150.1 (K), R150.2
unnamed: D150.2 (A), U20.5 (Q5)
unnamed: D151.1 (K), R151.2
unnamed: D151.2 (A), U20.6 (Q6)
unnamed: D152.1 (K), R152.2
unnamed: D152.2 (A), U20.7 (Q7)
unnamed: D153.1 (K), R153.2
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
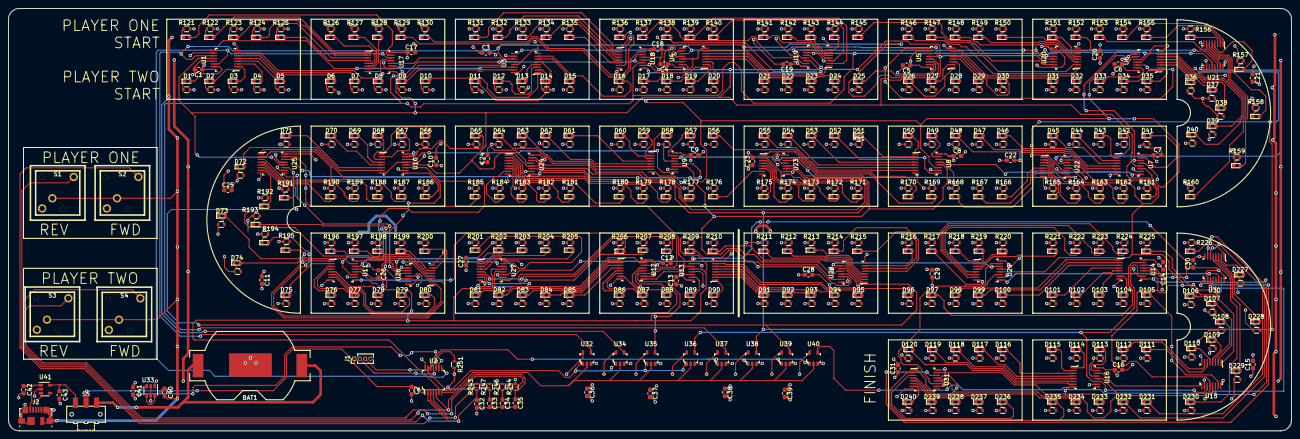
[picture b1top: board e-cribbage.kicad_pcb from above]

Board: 2 copper layers, 304.8 x 100.3 mm, 577 parts (0 on the bottom side), 534 nets.

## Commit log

2020-06-29 PBA parts placement
2020-06-29 reduced 0603 footprints
2020-06-29 power and ground planes added 471 nets unconnected
2020-06-29 updated schematic
2020-06-30 preliminary part placement and route
2020-06-30 updated digikey footprints with 3d models
2020-06-30 3D image
2020-06-30 MSP430 code examples and template added re-using UART to SPI program as starting point
2020-06-30 clock fanout added to schematic
2020-07-01 OE pulled low
2020-07-01 added datasheets and BOM
2020-07-01 added FET connector
2020-07-01 created local library
2020-07-01 schematic fixes + routes + battery clip
2020-07-01 clock routing
2020-07-02 schematic fix + more clock routes
2020-07-02 updated header comments
2020-07-02 more clock routes
2020-07-05 initial routing complete
2020-07-09 Schematic Update: USB Connector, Power Switch, Load Switch
2020-07-17 schematic updates - added 3.3V Linear Regulator
2020-07-17 Layout - routed switch, usb, linear reg
2020-07-22 Schematic Updates - SMT Batt/USB switch, 3.3V LDO, RCLCK connections to shift regs Library Updates - added 3D models for switches and battery
2020-07-24 Layout: routed USB power and switch, silkscreen
2020-07-24 updated 3D image
2020-07-24 image update
2020-07-26 Finished RCLK routes
2020-07-27 CCS project created
2020-07-27 Added Debug to tracked files
2020-07-28 established basic peg counting
2020-07-29 implemented sleep timer and wake up
2020-07-29 implemented restart, fixed point subraction bug, code cleanup
2020-07-29 implemented winner pattern
2020-07-29 implmented save and restore ***not yet tested***
2020-07-29 added to-do list to readme
2020-07-29 fixed broken connection on U24-14
2020-07-29 BOM export from Schematic
2020-07-30 schematic and parts cleanup
2020-07-30 BOM and parts updates
2020-07-30 replaced S1 with TH push button
2020-07-30 library and layout cleanup
2020-07-30 gerbers generated PCB order W100671ASM2 submitted
2020-08-11 Update README.md
    progress update
2020-08-11 Update README.md
    added software tasks
2020-08-12 debug and feature adds
    fixed backward pegging
    fixed P1/P2 swap
    fixed backward counting
    added play timer
    added game win counters
    added peg swap timer
2020-08-14 code cleanup
2020-08-19 added features: win total, save game, restore game
2020-09-03 code cleanup, fixed power-up glitch, optimized long press time
2020-09-03 removed function calls from main
2020-09-06 code clean up and bug fixes
    swapped player buttons and LE1/LE2 assignments
    fixed win total display bug
    fixed wakeup bug
